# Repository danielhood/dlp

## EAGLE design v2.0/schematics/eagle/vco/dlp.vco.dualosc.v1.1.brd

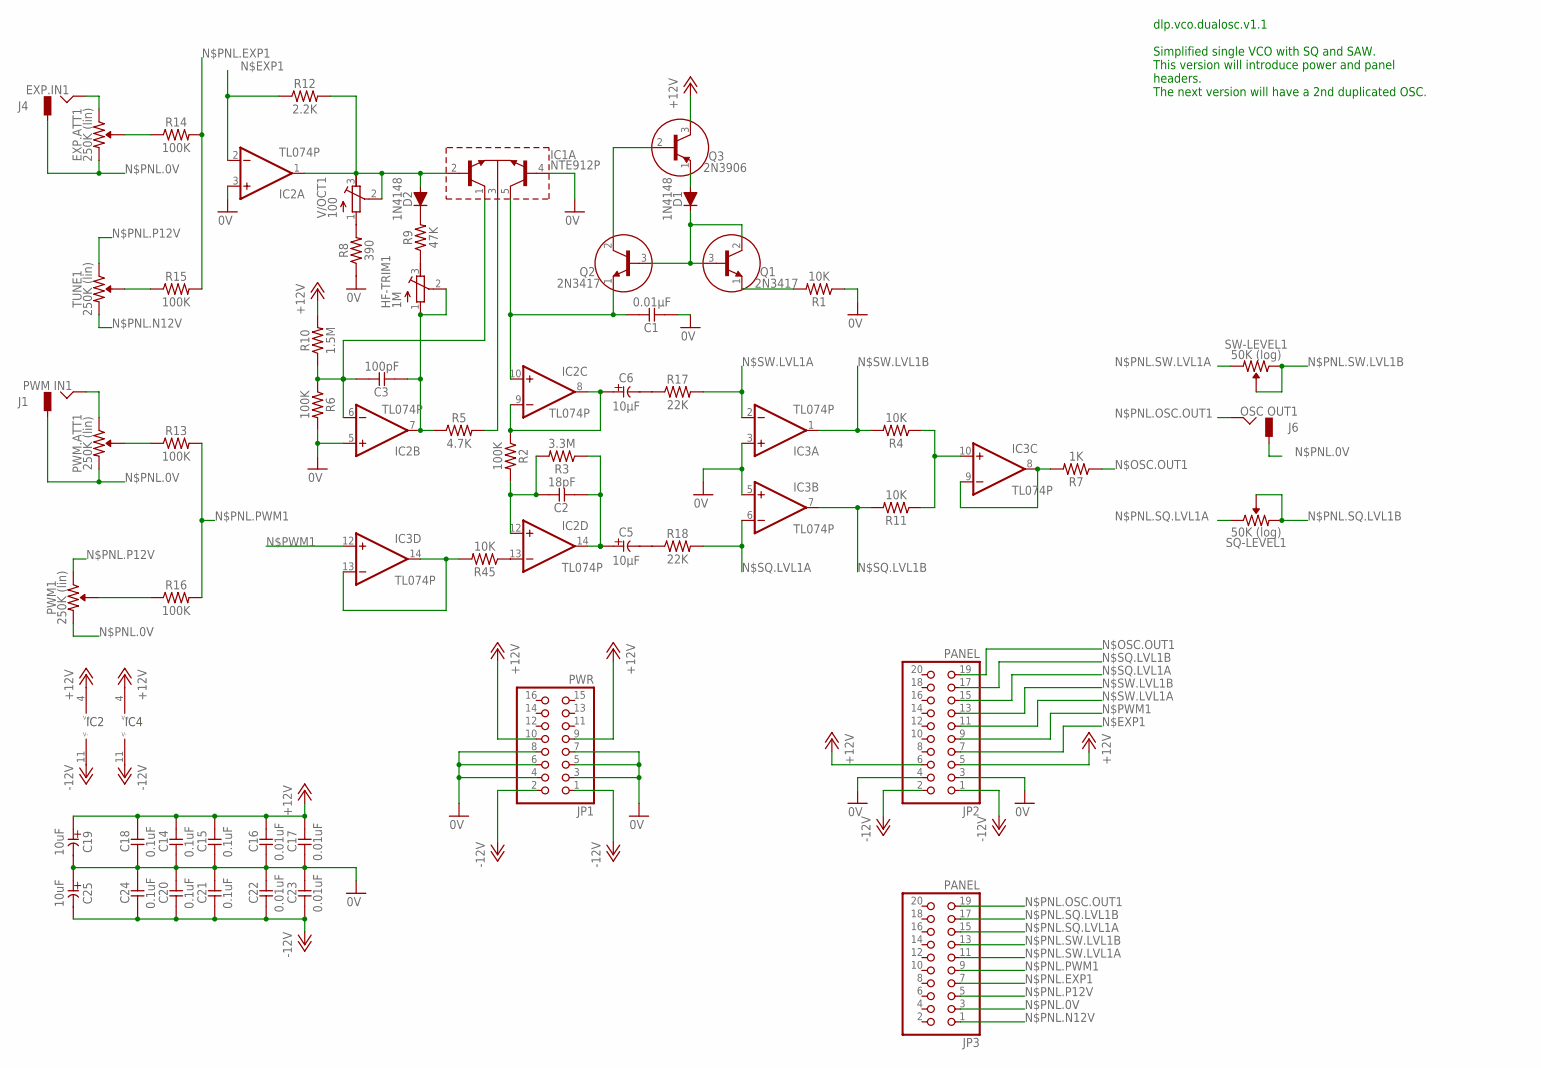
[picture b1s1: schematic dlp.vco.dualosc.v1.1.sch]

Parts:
C1: 0.01μF; C025-024X044
C2: 18pF; C025-024X044
C3: 100pF; C025-024X044
C5, C6: 10μF; E2-5
C14, C15, C18, C20, C21, C24: 0.1uF; C025-024X044
C16, C17, C22, C23: 0.01uF; C025-024X044
C19, C25: 10uF; E2-5
D1, D2: 1N4148; DO35-7
EXP.ATT1: 250K (lin); R-VAR
HF-TRIM1: 1M; RTRIM3296Y
IC1: NTE912P; DIL14
IC2, IC3: TL074P; DIL14
J1: PWM IN1; JACK-M
J4: EXP.IN1; JACK-M
J6: OSC OUT1; JACK-M
JP1: PWR; 2X08
JP2, JP3: PANEL; 2X10
PWM1, PWM.ATT1: 250K (lin); R-VAR
Q1, Q2: 2N3417; TO92
Q3: 2N3906; TO92
R1, R4, R11, R45: 10K; 0309/10
R2, R6, R13, R14, R15, R16: 100K; 0309/10
R3: 3.3M; 0309/10
R5: 4.7K; 0309/10
R7: 1K; 0309/10
R8: 390; 0309/10
R9: 47K; 0309/10
R10: 1.5M; 0309/10
R12: 2.2K; 0309/10
R17, R18: 22K; 0309/10
SQ-LEVEL1: 50K (log); R-VAR
SW-LEVEL1: 50K (log); R-VAR
TUNE1: 250K (lin); R-VAR
V/OCT1: 100; RTRIM3296Y

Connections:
0V: C1.2, C14.2, C15.2, C16.2, C17.2, C18.2, C19.-, C20.1, C21.1, C22.1, C23.1, C24.1, C25.+, IC1.4 (B3), IC2.3 (+IN), IC2.5 (+IN), IC3.3 (+IN), IC3.5 (+IN), JP1.3, JP1.4, JP1.5, JP1.6, JP1.7, JP1.8, JP2.3, JP2.4, R1.1, R6.2, R8.1
+12V: C14.1, C15.1, C16.1, C17.1, C18.1, C19.+, IC2.4 (V+), IC3.4 (V+), JP1.9, JP1.10, JP2.5, JP2.6, Q3.3 (C), R10.2
-12V: C20.2, C21.2, C22.2, C23.2, C24.2, C25.-, IC2.11 (V-), IC3.11 (V-), JP1.1, JP1.2, JP2.1, JP2.2
unnamed: C1.1, IC1.5 (C3), IC2.10 (+IN), Q2.1 (E)
unnamed: Q2.2 (C), Q3.2 (B)
unnamed: D1.A, Q3.1 (E)
unnamed: C6.+, IC2.8 (OUT), IC2.9 (-IN), R2.1
unnamed: D1.C, Q1.2 (C), Q1.3 (B), Q2.3 (B)
unnamed: Q1.1 (E), R1.2
unnamed: C2.1, IC2.12 (+IN), R2.2, R3.2
unnamed: IC2.13 (-IN), R45.1
unnamed: C2.2, C5.+, IC2.14 (OUT), R3.1
unnamed: PWM.ATT1.VAR, R13.1
unnamed: IC1.3 (E), R5.2
unnamed: D2.C, R9.2
unnamed: R8.2, V/OCT1.1 (A)
unnamed: C3.1, IC1.1 (C1), IC2.6 (-IN), R6.1, R10.1
unnamed: D2.A, IC1.2 (B1), IC2.1 (OUT), R12.2, V/OCT1.2 (S), V/OCT1.3 (E)
unnamed: HF-TRIM1.3 (E), R9.1
unnamed: IC3.10 (+IN), R4.1, R11.1
unnamed: PWM1.VAR, R16.1
unnamed: IC3.8 (OUT), IC3.9 (-IN), R7.2
unnamed: EXP.ATT1.VAR, R14.1
unnamed: R15.1, TUNE1.VAR
unnamed: J1.HOT, PWM.ATT1.R1 (1)
unnamed: EXP.ATT1.R1 (1), J4.HOT
unnamed: IC3.13 (-IN), IC3.14 (OUT), R45.2
unnamed: C6.-, R17.1
unnamed: C5.-, R18.1
unnamed: C3.2, HF-TRIM1.1 (A), HF-TRIM1.2 (S), IC2.7 (OUT), R5.1
N$EXP1: IC2.2 (-IN), JP2.7, R12.1
N$OSC.OUT1: JP2.19, R7.1
N$PNL.0V: EXP.ATT1.R2 (2), J1.GND, J4.GND, J6.GND, JP3.3, PWM1.R2 (2), PWM.ATT1.R2 (2)
N$PNL.EXP1: JP3.7, R14.2, R15.2
N$PNL.N12V: JP3.1, TUNE1.R2 (2)
N$PNL.OSC.OUT1: J6.HOT, JP3.19
N$PNL.P12V: JP3.5, PWM1.R1 (1), TUNE1.R1 (1)
N$PNL.PWM1: JP3.9, R13.2, R16.2
N$PNL.SQ.LVL1A: JP3.15, SQ-LEVEL1.R1 (1)
N$PNL.SQ.LVL1B: JP3.17, SQ-LEVEL1.R2 (2), SQ-LEVEL1.VAR
N$PNL.SW.LVL1A: JP3.11, SW-LEVEL1.R2 (2)
N$PNL.SW.LVL1B: JP3.13, SW-LEVEL1.R1 (1), SW-LEVEL1.VAR
N$PWM1: IC3.12 (+IN), JP2.9
N$SQ.LVL1A: IC3.6 (-IN), JP2.15, R18.2
N$SQ.LVL1B: IC3.7 (OUT), JP2.17, R11.2
N$SW.LVL1A: IC3.2 (-IN), JP2.11, R17.2
N$SW.LVL1B: IC3.1 (OUT), JP2.13, R4.2

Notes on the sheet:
IC2
IC4
dlp.vco.dualosc.v1.1 Simplified single VCO with SQ and SAW. This version will introduce power and panel headers. The next version will have a 2nd duplicated OSC.

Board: 2 copper layers, 58 parts (0 on the bottom side), 47 nets, no tracks yet.

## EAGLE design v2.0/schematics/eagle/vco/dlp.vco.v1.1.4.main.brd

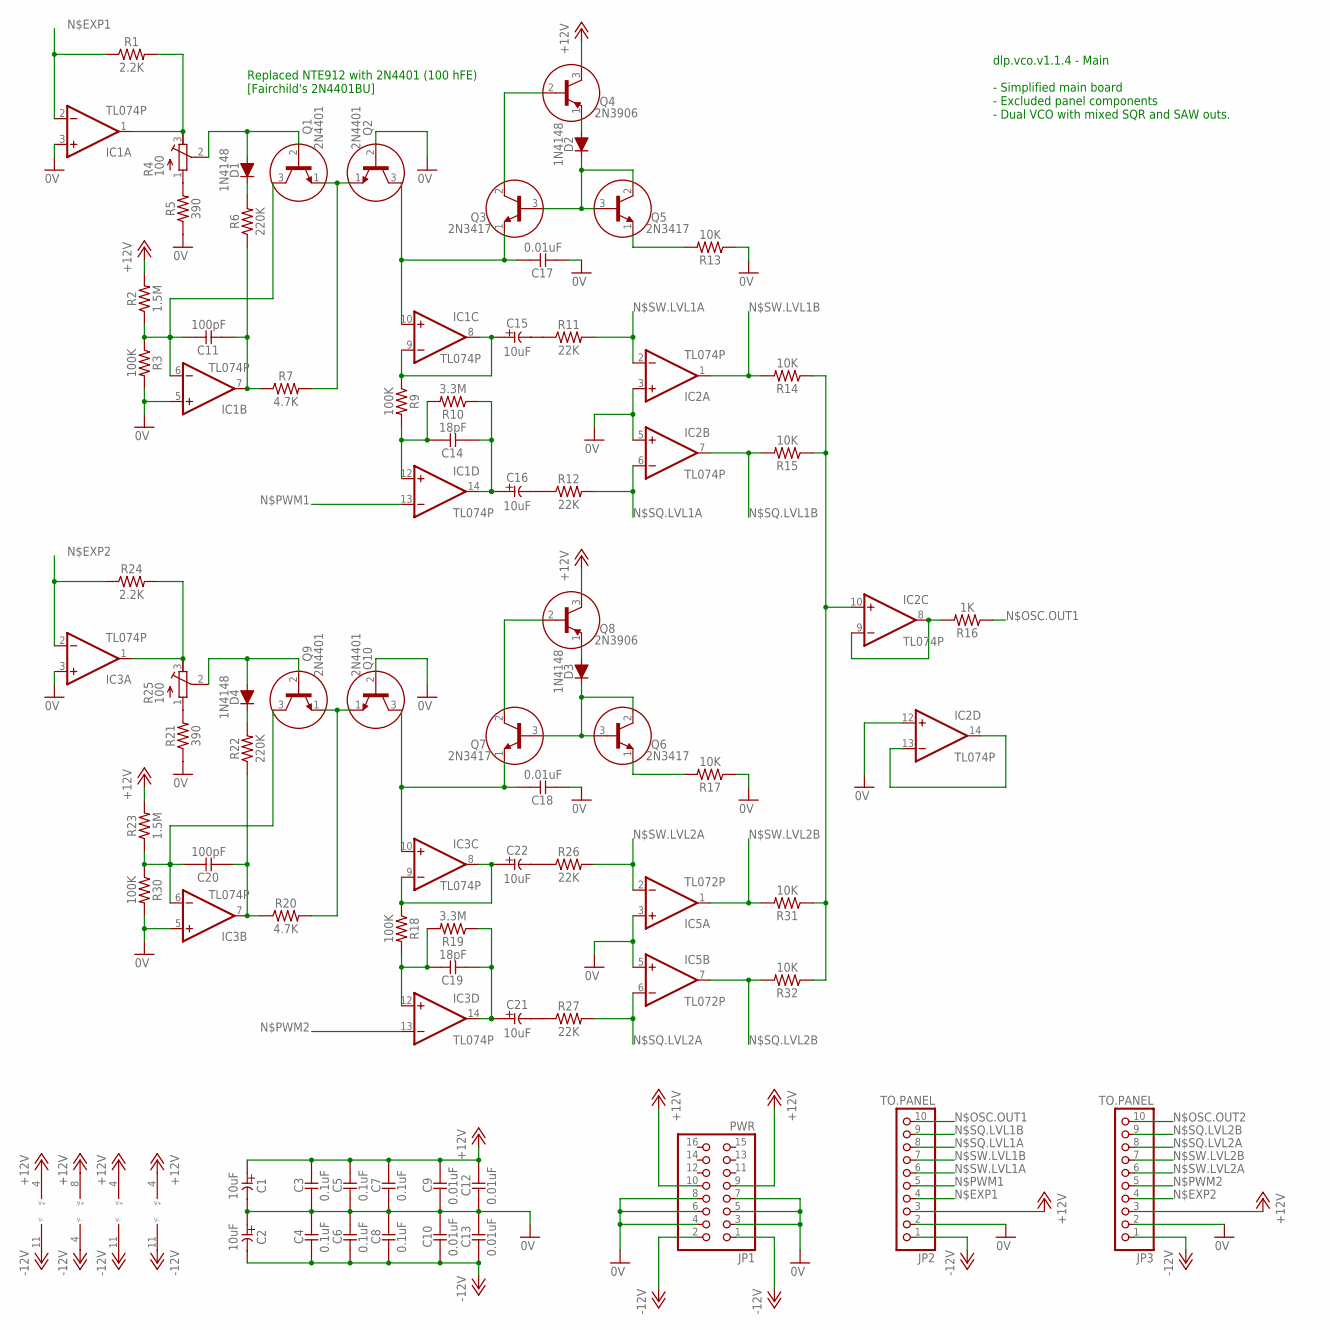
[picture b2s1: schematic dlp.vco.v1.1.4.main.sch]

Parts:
C1, C2, C15, C16, C21, C22: 10uF; E2-5
C3, C4, C5, C6, C7, C8: 0.1uF; C025-024X044
C9, C10, C12, C13, C17, C18: 0.01uF; C025-024X044
C11, C20: 100pF; C025-024X044
C14, C19: 18pF; C025-024X044
D1, D2, D3, D4: 1N4148; DO35-7
IC1, IC2, IC3: TL074P; DIL14
IC5: TL072P; DIL08
JP1: PWR; 2X08
JP2, JP3: TO.PANEL; 1X10
Q1, Q2, Q9, Q10: 2N4401; TO92
Q3, Q5, Q6, Q7: 2N3417; TO92
Q4, Q8: 2N3906; TO92
R1, R24: 2.2K; 0309/10
R2, R23: 1.5M; 0309/10
R3, R9, R18, R30: 100K; 0309/10
R4, R25: 100; RTRIM3296Y
R5, R21: 390; 0309/10
R6, R22: 220K; 0309/10
R7, R20: 4.7K; 0309/10
R10, R19: 3.3M; 0309/10
R11, R12, R26, R27: 22K; 0309/10
R13, R14, R15, R17, R31, R32: 10K; 0309/10
R16: 1K; 0309/10

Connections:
0V: C1.-, C2.+, C3.2, C4.1, C5.2, C6.1, C7.2, C8.1, C9.2, C10.1, C12.2, C13.1, C17.2, C18.2, IC1.3 (+IN), IC1.5 (+IN), IC2.3 (+IN), IC2.5 (+IN), IC2.12 (+IN), IC3.3 (+IN), IC3.5 (+IN), IC5.3 (+IN), IC5.5 (+IN), JP1.3, JP1.4, JP1.5, JP1.6, JP1.7, JP1.8, JP2.2, JP3.2, Q2.2 (B), Q10.2 (B), R3.2, R5.1, R13.1, R17.1, R21.1, R30.2
+12V: C1.+, C3.1, C5.1, C7.1, C9.1, C12.1, IC1.4 (V+), IC2.4 (V+), IC3.4 (V+), IC5.8 (V+), JP1.9, JP1.10, JP2.3, JP3.3, Q4.3 (C), Q8.3 (C), R2.2, R23.2
-12V: C2.-, C4.2, C6.2, C8.2, C10.2, C13.2, IC1.11 (V-), IC2.11 (V-), IC3.11 (V-), IC5.4 (V-), JP1.1, JP1.2, JP2.1, JP3.1
unnamed: C17.1, IC1.10 (+IN), Q2.3 (C), Q3.1 (E)
unnamed: Q3.2 (C), Q4.2 (B)
unnamed: D2.A, Q4.1 (E)
unnamed: C15.+, IC1.8 (OUT), IC1.9 (-IN), R9.1
unnamed: D2.C, Q3.3 (B), Q5.2 (C), Q5.3 (B)
unnamed: Q5.1 (E), R13.2
unnamed: C14.1, IC1.12 (+IN), R9.2, R10.2
unnamed: IC2.13 (-IN), IC2.14 (OUT)
unnamed: C14.2, C16.+, IC1.14 (OUT), R10.1
unnamed: D1.A, Q1.2 (B), R4.2 (S)
unnamed: C18.1, IC3.10 (+IN), Q7.1 (E), Q10.3 (C)
unnamed: Q1.1 (E), Q2.1 (E), R7.2
unnamed: D1.C, R6.2
unnamed: R4.1 (A), R5.2
unnamed: C11.1, IC1.6 (-IN), Q1.3 (C), R2.1, R3.1
unnamed: IC1.1 (OUT), R1.2, R4.3 (E)
unnamed: D3.A, Q8.1 (E)
unnamed: IC2.10 (+IN), R14.1, R15.1, R31.1, R32.1
unnamed: Q6.1 (E), R17.2
unnamed: IC2.8 (OUT), IC2.9 (-IN), R16.2
unnamed: D3.C, Q6.2 (C), Q6.3 (B), Q7.3 (B)
unnamed: Q7.2 (C), Q8.2 (B)
unnamed: C22.+, IC3.8 (OUT), IC3.9 (-IN), R18.1
unnamed: C19.1, IC3.12 (+IN), R18.2, R19.2
unnamed: C19.2, C21.+, IC3.14 (OUT), R19.1
unnamed: Q9.1 (E), Q10.1 (E), R20.2
unnamed: D4.C, R22.2
unnamed: C15.-, R11.1
unnamed: C16.-, R12.1
unnamed: C20.1, IC3.6 (-IN), Q9.3 (C), R23.1, R30.1
unnamed: IC3.1 (OUT), R24.2, R25.3 (E)
unnamed: C22.-, R26.1
unnamed: C21.-, R27.1
unnamed: C11.2, IC1.7 (OUT), R6.1, R7.1
unnamed: R21.2, R25.1 (A)
unnamed: C20.2, IC3.7 (OUT), R20.1, R22.1
unnamed: D4.A, Q9.2 (B), R25.2 (S)
N$EXP1: IC1.2 (-IN), JP2.4, R1.1
N$EXP2: IC3.2 (-IN), JP3.4, R24.1
N$OSC.OUT1: JP2.10, R16.1
N$OSC.OUT2: JP3.10
N$PWM1: IC1.13 (-IN), JP2.5
N$PWM2: IC3.13 (-IN), JP3.5
N$SQ.LVL1A: IC2.6 (-IN), JP2.8, R12.2
N$SQ.LVL1B: IC2.7 (OUT), JP2.9, R15.2
N$SQ.LVL2A: IC5.6 (-IN), JP3.8, R27.2
N$SQ.LVL2B: IC5.7 (OUT), JP3.9, R32.2
N$SW.LVL1A: IC2.2 (-IN), JP2.6, R11.2
N$SW.LVL1B: IC2.1 (OUT), JP2.7, R14.2
N$SW.LVL2A: IC5.2 (-IN), JP3.6, R26.2
N$SW.LVL2B: IC5.1 (OUT), JP3.7, R31.2

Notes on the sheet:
dlp.vco.v1.1.4 - Main - Simplified main board - Excluded panel components - Dual VCO with mixed SQR and SAW outs.
Replaced NTE912 with 2N4401 (100 hFE) [Fairchild's 2N4401BU]

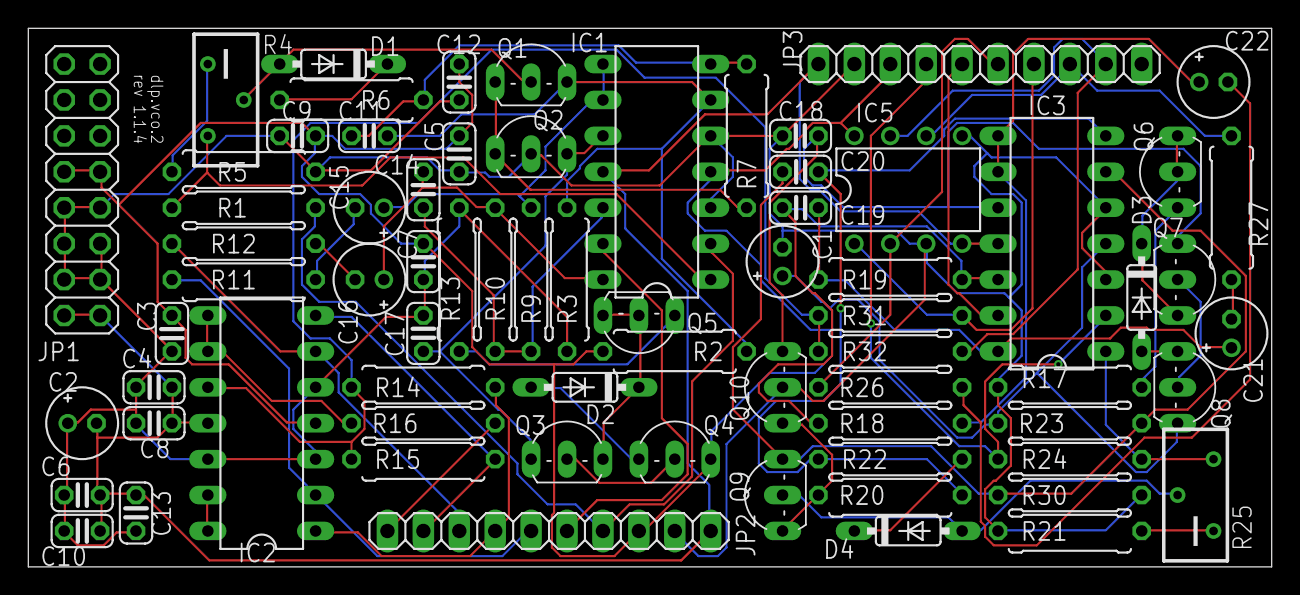
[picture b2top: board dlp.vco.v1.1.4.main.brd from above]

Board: 2 copper layers, 87.9 x 38.1 mm, 72 parts (0 on the bottom side), 53 nets.

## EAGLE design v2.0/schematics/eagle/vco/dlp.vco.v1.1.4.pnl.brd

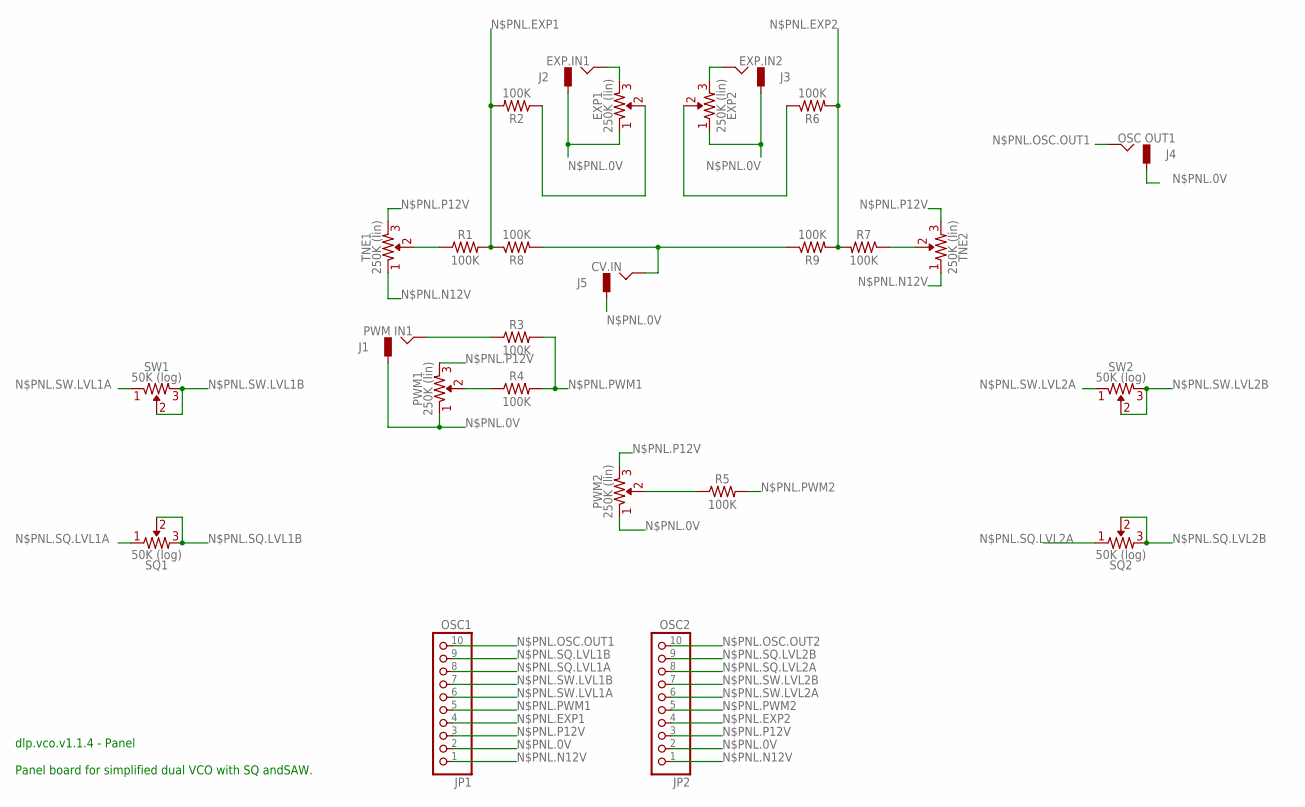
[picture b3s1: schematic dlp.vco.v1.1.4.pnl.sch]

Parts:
EXP1, EXP2: 250K (lin); R-VAR
J1: PWM IN1; JACK-M
J2: EXP.IN1; JACK-M
J3: EXP.IN2; JACK-M
J4: OSC OUT1; JACK-M
J5: CV.IN; JACK-M
JP1: OSC1; 1X10
JP2: OSC2; 1X10
PWM1, PWM2: 250K (lin); R-VAR
R1, R2, R3, R4, R5, R6, R7, R8, R9: 100K; 0309/10
SQ1, SQ2: 50K (log); R-VAR
SW1, SW2: 50K (log); R-VAR
TNE1, TNE2: 250K (lin); R-VAR

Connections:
unnamed: J5.HOT, R8.2, R9.1
unnamed: EXP1.VAR, R2.1
unnamed: R7.1, TNE2.VAR
unnamed: EXP1.R2 (2), J2.HOT
unnamed: EXP2.VAR, R6.1
unnamed: EXP2.R2 (2), J3.HOT
unnamed: J1.HOT, R3.1
unnamed: PWM1.VAR, R4.1
unnamed: PWM2.VAR, R5.1
unnamed: R1.1, TNE1.VAR
N$PNL.0V: EXP1.R1 (1), EXP2.R1 (1), J1.GND, J2.GND, J3.GND, J4.GND, J5.GND, JP1.2, JP2.2, PWM1.R1 (1), PWM2.R1 (1)
N$PNL.EXP1: JP1.4, R1.2, R2.2, R8.1
N$PNL.EXP2: JP2.4, R6.2, R7.2, R9.2
N$PNL.N12V: JP1.1, JP2.1, TNE1.R1 (1), TNE2.R1 (1)
N$PNL.OSC.OUT1: J4.HOT, JP1.10
N$PNL.OSC.OUT2: JP2.10
N$PNL.P12V: JP1.3, JP2.3, PWM1.R2 (2), PWM2.R2 (2), TNE1.R2 (2), TNE2.R2 (2)
N$PNL.PWM1: JP1.5, R3.2, R4.2
N$PNL.PWM2: JP2.5, R5.2
N$PNL.SQ.LVL1A: JP1.8, SQ1.R1 (1)
N$PNL.SQ.LVL1B: JP1.9, SQ1.R2 (2), SQ1.VAR
N$PNL.SQ.LVL2A: JP2.8, SQ2.R1 (1)
N$PNL.SQ.LVL2B: JP2.9, SQ2.R2 (2), SQ2.VAR
N$PNL.SW.LVL1A: JP1.6, SW1.R1 (1)
N$PNL.SW.LVL1B: JP1.7, SW1.R2 (2), SW1.VAR
N$PNL.SW.LVL2A: JP2.6, SW2.R1 (1)
N$PNL.SW.LVL2B: JP2.7, SW2.R2 (2), SW2.VAR

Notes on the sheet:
dlp.vco.v1.1.4 - Panel Panel board for simplified dual VCO with SQ andSAW.

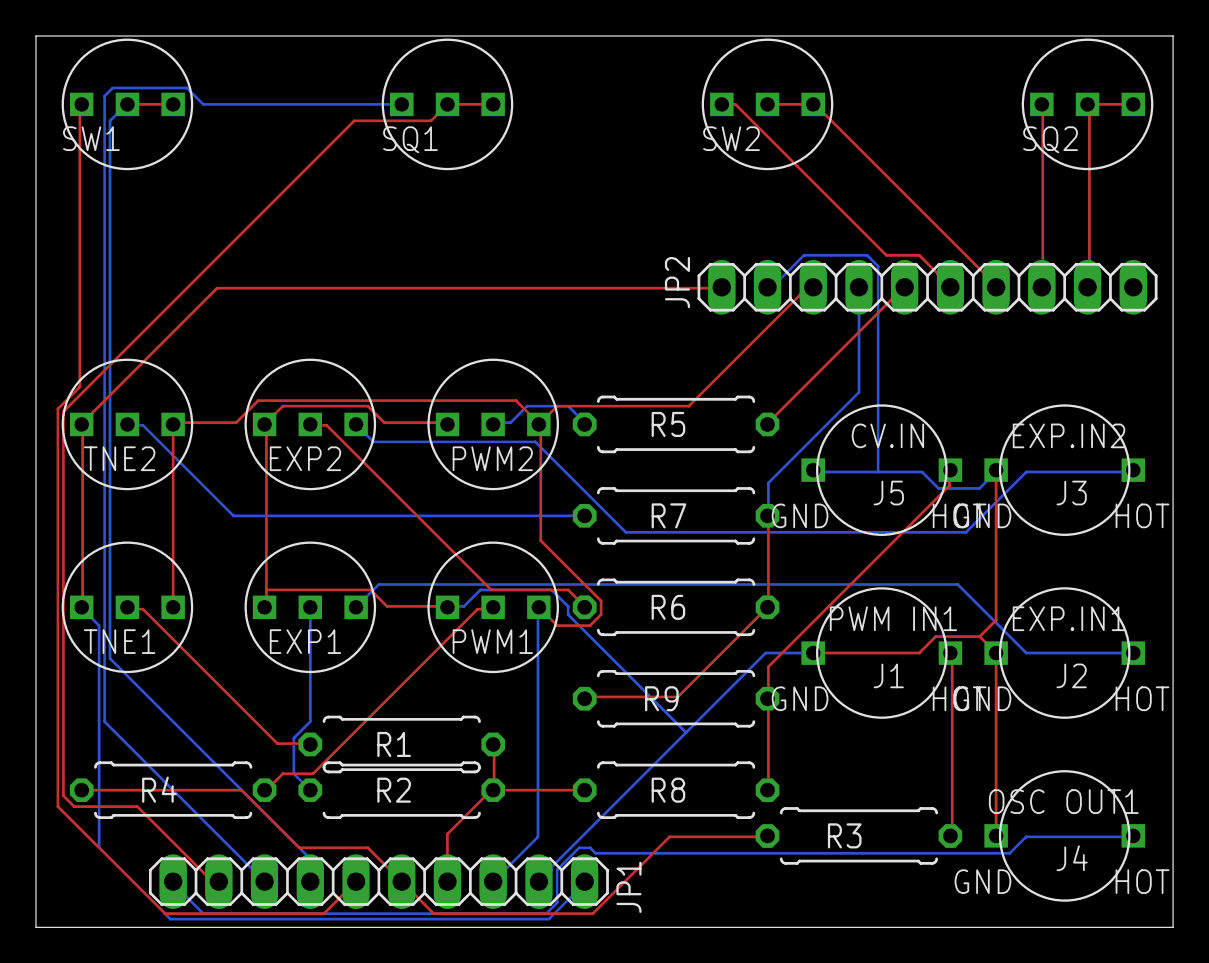
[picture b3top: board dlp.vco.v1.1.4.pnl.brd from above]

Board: 2 copper layers, 63.2 x 49.5 mm, 26 parts (0 on the bottom side), 26 nets.
